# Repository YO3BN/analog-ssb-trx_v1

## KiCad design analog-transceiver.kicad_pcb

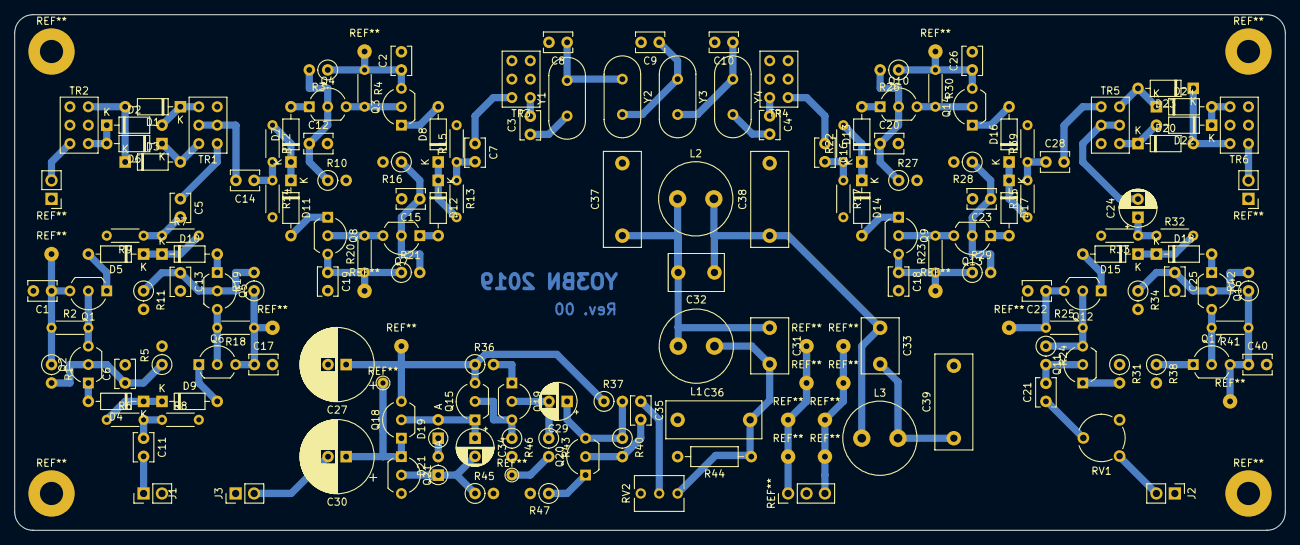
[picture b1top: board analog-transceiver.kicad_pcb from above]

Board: 2 copper layers, 175.3 x 71.1 mm, 150 parts (0 on the bottom side), 89 nets.

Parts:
C1, C2, C6, C7, C12, C13, C14, C15, C16, C17, C18, C19, C20, C21, C22, C23, C25, C26, C28, C35, C40: 100n; C_Disc_D3.8mm_W2.6mm_P2.50mm
C3, C4, C8, C9, C10: 0; C_Disc_D3.8mm_W2.6mm_P2.50mm
C5, C11: 1u; C_Disc_D3.8mm_W2.6mm_P2.50mm
C24, C29: 10u; CP_Radial_D5.0mm_P2.50mm
C27, C30: 220u; CP_Radial_D10.0mm_P2.50mm
C31, C32, C33: 0; C_Disc_D7.5mm_W5.0mm_P5.00mm
C34: 1u; CP_Radial_D5.0mm_P2.50mm
C36, C37, C38, C39: 0; C_Rect_L13.0mm_W5.0mm_P10.00mm_FKS3_FKP3_MKS4
D1, D2, D3, D6, D20, D22, D23, D24: BAT41; D_DO-35_SOD27_P7.62mm_Horizontal
D4, D5, D7, D8, D9, D10, D11, D12, D13, D14, D15, D16, D17, D18: 1N4148; D_DO-35_SOD27_P7.62mm_Horizontal
D19, D21: 1N4148; D_DO-35_SOD27_P2.54mm_Vertical_AnodeUp
J1: BNC; PinHeader_1x02_P2.54mm_Vertical
J2: AF In; PinHeader_1x02_P2.54mm_Vertical
J3: AF Out; PinHeader_1x02_P2.54mm_Vertical
L1, L2, L3: 0; L_Radial_D10.0mm_P5.00mm_Neosid_SD12k_style3
Q1, Q2, Q3, Q4, Q5, Q6, Q7, Q8, Q9, Q10, Q11, Q12, Q13, Q14, Q15, Q16, Q17, Q18, Q20: 2N3904; TO-92_Inline_Wide
Q19, Q21: 2N3906; TO-92_Inline_Wide
R1, R3, R5, R10, R11, R16, R19, R21, R26, R27, R28, R29, R34, R38, R42: 0; R_Axial_DIN0207_L6.3mm_D2.5mm_P2.54mm_Vertical
R2, R4, R18, R20, R23, R30, R41: 680; R_Axial_DIN0204_L3.6mm_D1.6mm_P5.08mm_Horizontal
R6, R7, R12, R13, R22, R32, R35: 47; R_Axial_DIN0204_L3.6mm_D1.6mm_P5.08mm_Horizontal
R8, R9, R14, R15, R17, R33, R39: 390; R_Axial_DIN0204_L3.6mm_D1.6mm_P5.08mm_Horizontal
R24: 1M5?; R_Axial_DIN0207_L6.3mm_D2.5mm_P2.54mm_Vertical
R25: 2k2; R_Axial_DIN0204_L3.6mm_D1.6mm_P5.08mm_Horizontal
R31, R47: 220; R_Axial_DIN0207_L6.3mm_D2.5mm_P2.54mm_Vertical
R36: 270; R_Axial_DIN0207_L6.3mm_D2.5mm_P2.54mm_Vertical
R37: 2k2; R_Axial_DIN0207_L6.3mm_D2.5mm_P2.54mm_Vertical
R40: 1M5; R_Axial_DIN0207_L6.3mm_D2.5mm_P2.54mm_Vertical
R43: 330k; R_Axial_DIN0207_L6.3mm_D2.5mm_P2.54mm_Vertical
R44: 0; R_Axial_DIN0207_L6.3mm_D2.5mm_P10.16mm_Horizontal
R45: 1k; R_Axial_DIN0207_L6.3mm_D2.5mm_P2.54mm_Vertical
R46: 2k7; R_Axial_DIN0207_L6.3mm_D2.5mm_P2.54mm_Vertical
RV1: 10K; Potentiometer_Piher_PT-6-V_Vertical
RV2: 0; Potentiometer_Vishay_T73XW_Horizontal
TR1, TR2, TR5, TR6: 3x7 43-binocular; SW_NKK_G1xJP
TR3, TR4: ADT16-6; SW_NKK_G1xJP
Y1, Y2, Y3, Y4: 10MHz; Crystal_HC49-U_Vertical

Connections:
+RX: C1.1, C2.1, C26.1, C27.1, C40.1, Q1.3, Q3.3, Q14.3, Q15.3, Q17.3, Q18.3, R1.1, R2.1, R3.1, R4.1, R26.1, R30.1, R36.1, R37.1, R41.1, R42.1
+TX: C17.1, C18.1, C19.1, C22.1, Q6.3, Q8.3, Q9.3, Q12.3, R18.1, R19.1, R20.1, R21.1, R23.1, R25.1, R29.1, RV1.1
GND: C1.2, C2.2, C6.2, C8.2, C9.2, C10.2, C12.2, C13.2, C15.2, C17.2, C18.2, C19.2, C20.2, C22.2, C23.2, C25.2, C26.2, C27.2, C36.1, C37.2, C38.2, C39.2, C40.2, J1.2, J2.1, J3.1, Q21.3, R5.2, R8.2, R9.2, R10.2, R11.2, R14.2, R15.2, R16.2, R17.2, R27.2, R28.2, R31.1, R33.2, R34.2, R39.2, R44.2, R45.2, R46.2, R47.2, RV2.1, TR1.3, TR2.1, TR2.2, TR2.5, TR3.3, TR3.4, TR4.3, TR4.4, TR5.3, TR6.2, TR6.3, TR6.5
unnamed: C3.1, Y1.1
unnamed: C3.2, TR3.1
unnamed: C4.1, TR4.6
unnamed: C4.2, Y4.2
unnamed: C5.1, TR1.1
unnamed: C5.2, R7.1, R9.1
unnamed: C6.1, Q2.2, R1.2, R5.1
unnamed: C7.1, TR3.6
unnamed: C7.2, R13.1, R15.1
unnamed: C8.1, Y1.2, Y2.1
unnamed: C9.1, Y2.2, Y3.1
unnamed: C10.1, Y3.2, Y4.1
unnamed: C11.1, R6.2, R8.1
unnamed: C11.2, J1.1
unnamed: C12.1, Q4.2, R3.2, R10.1
unnamed: C13.1, Q5.2, R11.1, R19.2
unnamed: C14.1, R12.2, R14.1
unnamed: C14.2, TR1.2, TR1.5
unnamed: C15.1, Q7.2, R16.1, R21.2
unnamed: C16.1, TR4.1
unnamed: C16.2, R17.1, R22.1
unnamed: C20.1, Q10.2, R26.2, R27.1
unnamed: C21.1, RV1.2
unnamed: C21.2, Q11.2, R24.2
unnamed: C23.1, Q13.2, R28.1, R29.2
unnamed: C24.1, R32.1, R33.1
unnamed: C24.2, TR5.2, TR5.5
unnamed: C25.1, Q16.2, R34.1, R42.2
unnamed: C28.1, R35.2, R39.1
unnamed: C28.2, TR5.1
unnamed: C29.1, Q20.3, R37.2, R40.1
unnamed: C29.2, Q19.2, R43.1
unnamed: C30.1, Q18.1, Q21.1, R43.2
unnamed: C30.2, J3.2
unnamed: C31.1, C32.2, C37.1, L1.2, L2.1
unnamed: C31.2, C36.2, L1.1, R44.1, RV2.3
unnamed: C32.1, C33.1, C38.1, L2.2, L3.1
unnamed: C33.2, C39.1, L3.2, R38.2
unnamed: C34.1, D19.2, Q15.1, Q18.2
unnamed: C34.2, D21.1, Q21.2, R45.1
unnamed: C35.1, RV2.2
unnamed: C35.2, Q20.2, R40.2
unnamed: D1.1, D2.2, TR1.4
unnamed: D1.2, D3.1, TR2.6
unnamed: D2.1, D6.2, TR2.4
unnamed: D3.2, D6.1, TR1.6
unnamed: D4.1, D9.1, R6.1
unnamed: D4.2, Q2.1
unnamed: D5.2, Q1.1
unnamed: D7.2, Q4.1
unnamed: D8.2, Q3.1
unnamed: D9.2, Q6.1
unnamed: D5.1, D10.1, R7.2
unnamed: D10.2, Q5.1
unnamed: D7.1, D11.1, R12.1
unnamed: D11.2, Q8.1
unnamed: D8.1, D12.1, R13.2
unnamed: D12.2, Q7.1
unnamed: D13.1, D14.1, R22.2
unnamed: D13.2, Q10.1
unnamed: D14.2, Q9.1
unnamed: D15.1, D18.1, R32.2
unnamed: D15.2, Q12.1
unnamed: D16.1, D17.1, R35.1
unnamed: D16.2, Q14.1
unnamed: D17.2, Q13.1
unnamed: D18.2, Q16.1
unnamed: D19.1, D21.2
unnamed: D20.1, D22.2, TR5.4
unnamed: D20.2, D23.1, TR6.6
unnamed: D22.1, D24.2, TR6.4
unnamed: D23.2, D24.1, TR5.6
unnamed: J2.2, RV1.3
unnamed: Q1.2, Q2.3, R2.2
unnamed: Q3.2, Q4.3, R4.2
unnamed: Q5.3, Q6.2, R18.2
unnamed: Q7.3, Q8.2, R20.2
unnamed: Q10.3, Q14.2, R30.2
unnamed: Q11.1, R31.2
unnamed: Q11.3, Q12.2, R24.1, R25.2
unnamed: Q9.2, Q13.3, R23.2
unnamed: Q15.2, Q19.3, R46.1
unnamed: Q16.3, Q17.2, R41.2
unnamed: Q17.1, R38.1
unnamed: Q19.1, R36.2
unnamed: Q20.1, R47.1

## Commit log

2022-10-12 First commit.
